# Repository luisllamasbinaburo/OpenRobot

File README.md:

# OpenRobot

OpenRobot is an Open Hardware PCB based on Arduino Nano, especially designed for teaching technology

Once assembled, you can use make multiple projects and robots without welding, just adding or removing components in the dupont headers.

OpenRobot is compatible with a huge number of modules thanks to the multiple outputs. 
Also, is compatible with several DC Converters, and differents IMUs (MPU6050, MPU9050/9250 and L3GD20)

## What can I make with OpenRobot?
Almost any Arduino project you can ever imagine! 

Some of them,
- DC Motors Robot, like obstacle avoider (ultrasonic or Sharp), line follower, self-balancing bot...
- Servo Motor Robot, like 2-DOF Tower, 6-DOF Arms...
- Mosfet output for high current proyects (LED, electromagnets, water pumps)
- Bluetooth projects (HC-05/HC-06), like Android or PC communication, beacons...
- WiFi projects (ESP01), like controlling from Web, MQTT datalogger...
- Temperature, pressure, humidity weather station with BME280
- Any other project, thanks to the multiple available outputs!

## Connectors
A lot of connectos availble, so you can customicce OpenRobot to you project requirement

- 2x DC Motor
- 2x Encoder
- Aux Output 3V3, 5V, Vreg
- 2x I2C 5V + 1x I2C 3V3
- 3x Ultrasonic Sensor
- 3x Analog Input (with optional smd resistor)
- 6x Servo
- 5x IR Sensor
- 3x Mosfet
 
 But, I you wany, can also use any of this output as a GPIO.

## Pinout
Of course, not all the components and outputs are available at the same time, due to Arduino Nano pins numbers.

You have to choose which of this components your project requires. But posibilities are almost ilimited!

This is the pinout of OpenRobot

## Components
OpenRobot allows you to mount several modules to your projects,
- Motor Driver TB6612FNG
- IMU (compatible with several IMUs)
- Temperature/Pressure/Humidity (BMP280/BME280)
- Level shifter (required to use Bluetooth or ESP01)
- Blueooth ESP01
- Bluetooth HC-04/05/06

But you can add a lot of modules thanks to the 3V3 and 5V I2C and UART.

## Powering
Powering is one of the most important point in any project. OpenRobot allow a simple but flexible power management in the proyect
- Power Switch 
- Up to 3 DC Converters (5V, 3V3, +1 Vreg)
- Power selector to select wich components (DC Motors, servo, Mosfet) are powering with each DC converter
- Posible to by-pass DC Converters and powering through Nano regulators (just in low-power and simple projects)
- Battery sense (optional)

### DC Converters
OpenRobot is compatible with two different DC Converters modules.

Just assembly in the right position for you DC Converter model.

### Power selection
Powering selection to device are make using dupong jumper connections.
Outputs to:
- Servo
- DC Motors
- Mosfet

Can be connected to:
- Vregulated
- 5V
- Vbatery

Aditionally, you can completely by-pass DC converters, and use Arduino regulators for 3V3 and/or 5V PCB rails, thus removing the need of installing DC Converters at all.

Only recommended in case of small / low power projects

## IMU
IMU is an important part of most Arduino projects. OpenRobot is compatible with a big number of IMUs, including the most populars. 

Just put your IMU in the right position. In some IMU modules you make need to use the Vcc optional pin to adapt powering to your IMU pinout.

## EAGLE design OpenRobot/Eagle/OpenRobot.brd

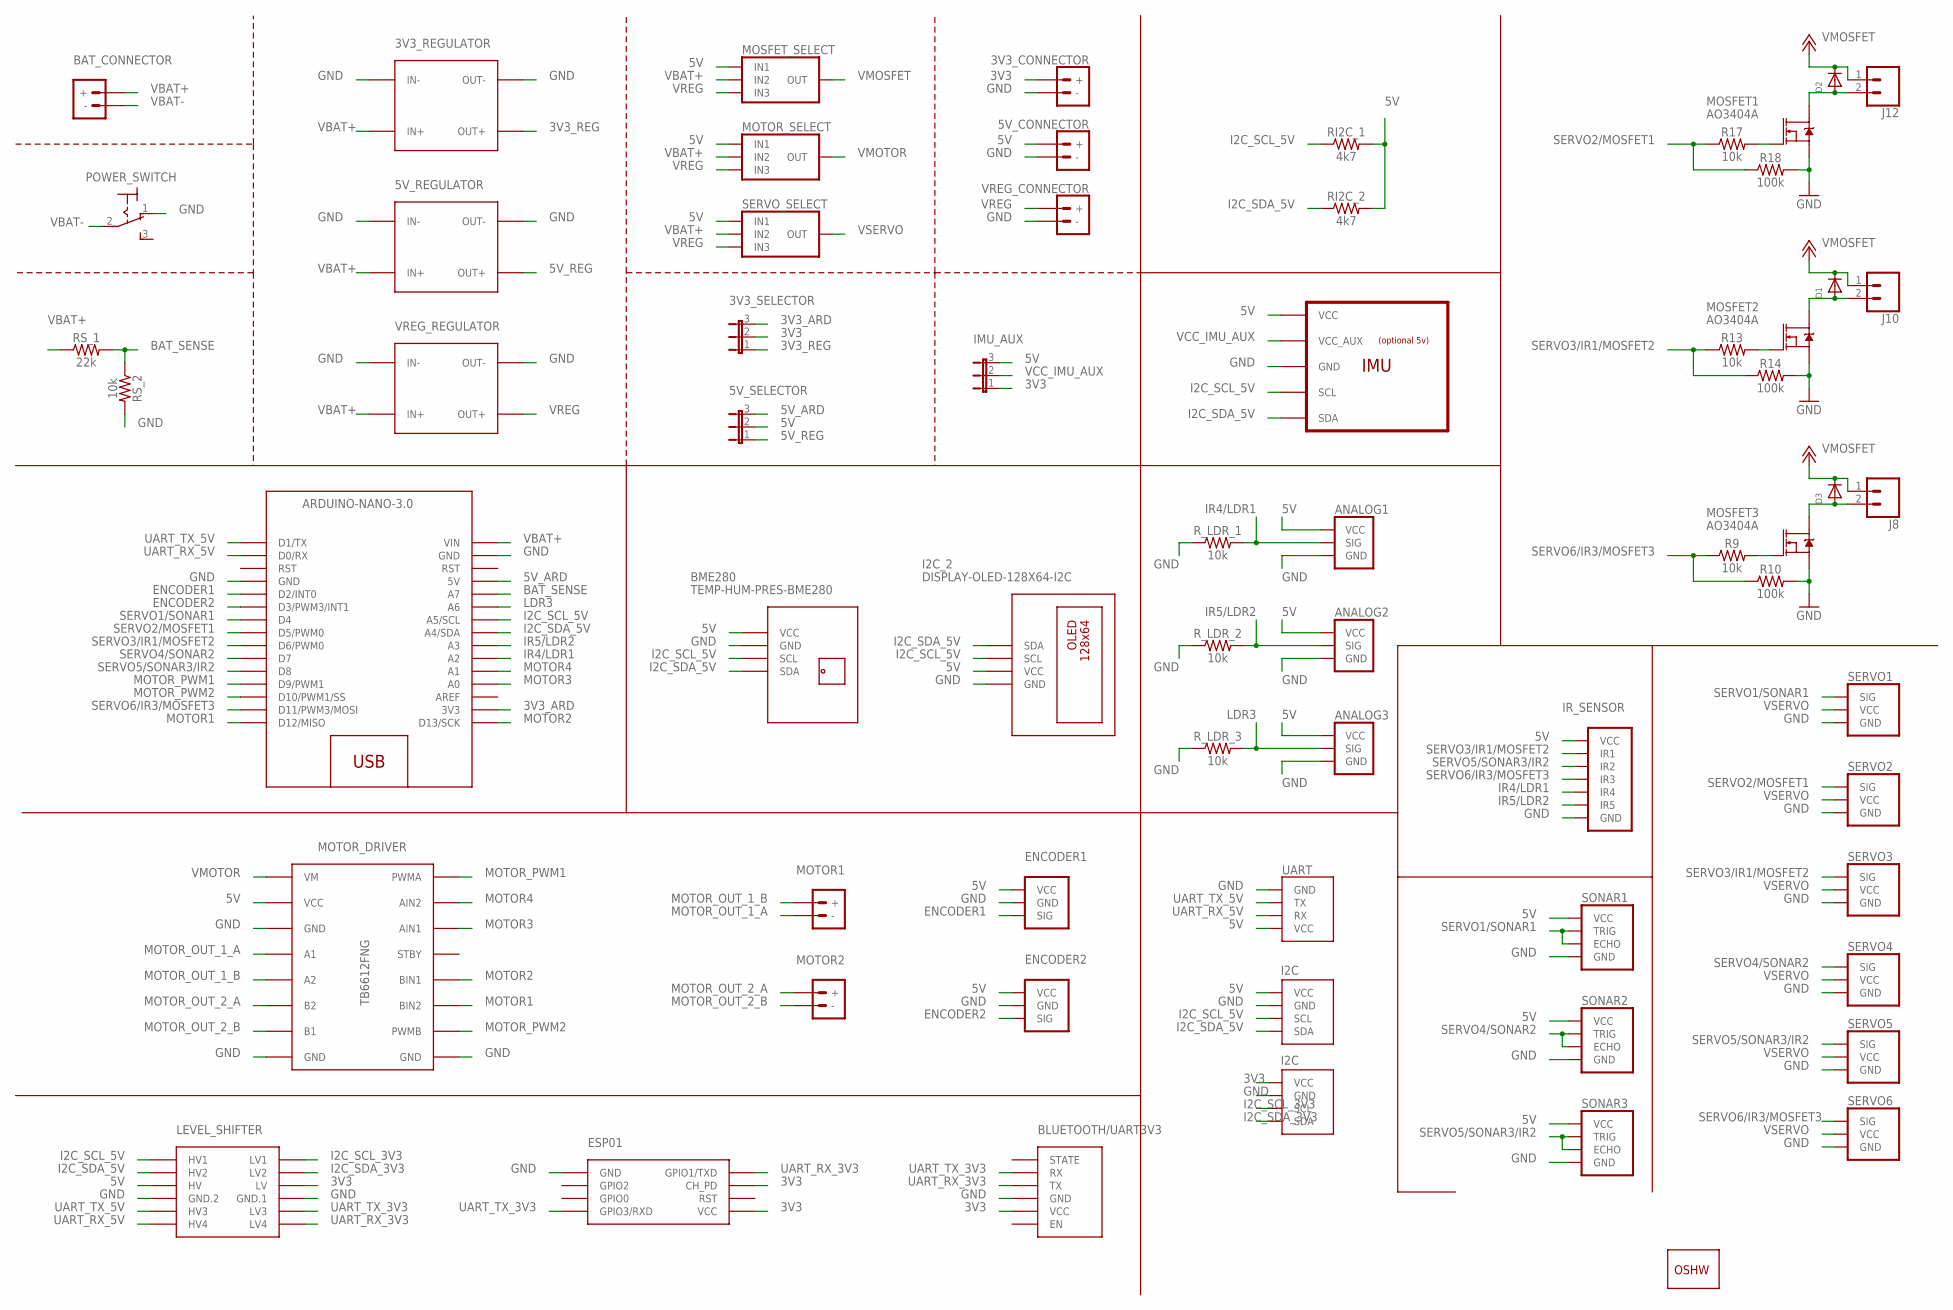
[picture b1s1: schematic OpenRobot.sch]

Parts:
3V3_CONNECTOR, 5V_CONNECTOR: MOTOR-TERMINAL2.54MM_SCREWTERM; 1X02_2.54_SCREWTERM
3V3_REGULATOR, 5V_REGULATOR: MINI-DC-STEP-DOWN-MP2307
3V3_SELECTOR, 5V_SELECTOR: 1; JP2
ANALOG1, ANALOG2, ANALOG3: LDR/OCT; LDR
ARDUINO_NANO1: ARDUINO-NANO-3.0
BAT_CONNECTOR: POWER-TERMINAL5MM; SCREWTERMINAL-5MM-2
BLUETOOTH/UART3V3: BLUETOOTH-HC-05
BME280: TEMP-HUM-PRES-BME280
D1, D2, D3: DIODESOD-123; SOD-123
ENCODER1, ENCODER2: ENCODER/OCT; ENCODER
GOLD_ORB_SM1: OSHWLOGO_GOLD_ORB_MED; OSHW1
I2C_1, I2C_3: I2C; I2C_VCC_GND_SCL_SDA
I2C_2: DISPLAY-OLED-128X64-I2C
IMU_AUX: 1; JP2
IR_SENSOR: IR-5/OCT; IR-5
J8, J10, J12: CONN_02LOCK_LONGPADS; 1X02_LOCK_LONGPADS
LEVEL_SHIFTER: LEVEL-SHIFTER-4CH
MOSFET1, MOSFET2, MOSFET3: AO3404A; SOT23-3
MOSFET_SELECT: JUMPER_3-1
MOTOR1, MOTOR2: MOTOR-TERMINAL5MM; SCREWTERMINAL-5MM-2
MOTOR_DRIVER: TB6612FNG
MOTOR_SELECT: JUMPER_3-1
POWER_SWITCH: LEVER-POWER-SWITCH; M9040P
R9, R13, R17: 10k; 1206
R10, R14, R18: 100k; 1206
RI2C_1, RI2C_2: 4k7; 1206
RS_1: 22k; 1206
RS_2: 10k; 1206
R_LDR_1, R_LDR_2, R_LDR_3: 10k; 1206
SERVO1, SERVO2, SERVO3, SERVO4, SERVO5, SERVO6: SERVOSERVO; SERVO
SERVO_SELECT: JUMPER_3-1
SONAR1, SONAR2, SONAR3: ULTRASONIC/OCT; ULTRASONIC
U1: IMU_6/9/10DOFMPU6050; IMU_6/9/10DOF
U$1: ESP01
UART: UART; GENERIC_UART
VREG_CONNECTOR: MOTOR-TERMINAL2.54MM_SCREWTERM; 1X02_2.54_SCREWTERM
VREG_REGULATOR: MINI-DC-STEP-DOWN-MP2307

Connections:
3V3: 3V3_CONNECTOR.+, 3V3_SELECTOR.2, BLUETOOTH/UART3V3.VCC, I2C_3.VCC, IMU_AUX.1, LEVEL_SHIFTER.J1.3 (LV), U$1.CH_PD, U$1.VCC
3V3_ARD: 3V3_SELECTOR.3, ARDUINO_NANO1.3V3
3V3_REG: 3V3_REGULATOR.OUT2.+ (OUT+), 3V3_REGULATOR.OUT+, 3V3_SELECTOR.1
5V: 5V_CONNECTOR.+, 5V_SELECTOR.2, ANALOG1.VCC, ANALOG2.VCC, ANALOG3.VCC, BME280.VCC, ENCODER1.VCC, ENCODER2.VCC, I2C_1.VCC, I2C_2.VCC, IMU_AUX.3, IR_SENSOR.VCC, LEVEL_SHIFTER.J2.3 (HV), MOSFET_SELECT.IN1, MOTOR_DRIVER.VCC, MOTOR_SELECT.IN1, RI2C_1.2, RI2C_2.2, SERVO_SELECT.IN1, SONAR1.VCC, SONAR2.VCC, SONAR3.VCC, U1.VCC, UART.VCC
5V_ARD: 5V_SELECTOR.3, ARDUINO_NANO1.5V
5V_REG: 5V_REGULATOR.OUT2.+ (OUT+), 5V_REGULATOR.OUT+, 5V_SELECTOR.1
BAT_SENSE: ARDUINO_NANO1.A7, RS_1.2, RS_2.1
ENCODER1: ARDUINO_NANO1.D2 (D2/INT0), ENCODER1.SIG
ENCODER2: ARDUINO_NANO1.D3 (D3/PWM3/INT1), ENCODER2.SIG
GND: 3V3_CONNECTOR.-, 3V3_REGULATOR.IN-, 3V3_REGULATOR.OUT-, 5V_CONNECTOR.-, 5V_REGULATOR.IN-, 5V_REGULATOR.OUT-, ANALOG1.GND, ANALOG2.GND, ANALOG3.GND, ARDUINO_NANO1.GND@1 (GND), ARDUINO_NANO1.GND@2 (GND), BLUETOOTH/UART3V3.GND, BME280.GND, ENCODER1.GND, ENCODER2.GND, I2C_1.GND, I2C_2.GND, I2C_3.GND, IR_SENSOR.GND, LEVEL_SHIFTER.J1.4 (GND.1), LEVEL_SHIFTER.J2.4 (GND.2), MOSFET1.2 (S), MOSFET2.2 (S), MOSFET3.2 (S), MOTOR_DRIVER.GND1 (GND), MOTOR_DRIVER.GND2 (GND), MOTOR_DRIVER.GND3 (GND), POWER_SWITCH.1 (O), R10.2, R14.2, R18.2, RS_2.2, R_LDR_1.1, R_LDR_2.1, R_LDR_3.1, SERVO1.GND, SERVO2.GND, SERVO3.GND, SERVO4.GND, SERVO5.GND, SERVO6.GND, SONAR1.GND, SONAR2.GND, SONAR3.GND, U1.GND, U$1.GND, UART.GND, VREG_CONNECTOR.-, VREG_REGULATOR.IN-, VREG_REGULATOR.OUT-
I2C_SCL_3V3: I2C_3.SCL, LEVEL_SHIFTER.J1.1 (LV1)
I2C_SCL_5V: ARDUINO_NANO1.A5 (A5/SCL), BME280.SCL, I2C_1.SCL, I2C_2.SCL, LEVEL_SHIFTER.J2.1 (HV1), RI2C_1.1, U1.SCL
I2C_SDA_3V3: I2C_3.SDA, LEVEL_SHIFTER.J1.2 (LV2)
I2C_SDA_5V: ARDUINO_NANO1.A4 (A4/SDA), BME280.SDA, I2C_1.SDA, I2C_2.SDA, LEVEL_SHIFTER.J2.2 (HV2), RI2C_2.1, U1.SDA
IR4/LDR1: ANALOG1.SIG, ARDUINO_NANO1.A2, IR_SENSOR.4 (IR4), R_LDR_1.2
IR5/LDR2: ANALOG2.SIG, ARDUINO_NANO1.A3, IR_SENSOR.5 (IR5), R_LDR_2.2
LDR3: ANALOG3.SIG, ARDUINO_NANO1.A6, R_LDR_3.2
MOTOR1: ARDUINO_NANO1.D12 (D12/MISO), MOTOR_DRIVER.BIN2
MOTOR2: ARDUINO_NANO1.D13 (D13/SCK), MOTOR_DRIVER.BIN1
MOTOR3: ARDUINO_NANO1.A0, MOTOR_DRIVER.AIN1
MOTOR4: ARDUINO_NANO1.A1, MOTOR_DRIVER.AIN2
MOTOR_OUT_1_A: MOTOR1.-, MOTOR_DRIVER.A1
MOTOR_OUT_1_B: MOTOR1.+, MOTOR_DRIVER.A2
MOTOR_OUT_2_A: MOTOR2.+, MOTOR_DRIVER.B2
MOTOR_OUT_2_B: MOTOR2.-, MOTOR_DRIVER.B1
MOTOR_PWM1: ARDUINO_NANO1.D9 (D9/PWM1), MOTOR_DRIVER.PWMA
MOTOR_PWM2: ARDUINO_NANO1.D10 (D10/PWM1/SS), MOTOR_DRIVER.PWMB
unnamed: MOSFET3.1 (G), R9.2
unnamed: D3.A, J8.2, MOSFET3.3 (D)
unnamed: MOSFET2.1 (G), R13.2
unnamed: D1.A, J10.2, MOSFET2.3 (D)
unnamed: MOSFET1.1 (G), R17.2
unnamed: D2.A, J12.2, MOSFET1.3 (D)
SERVO1/SONAR1: ARDUINO_NANO1.D4, SERVO1.SIG, SONAR1.ECHO, SONAR1.TRIG
SERVO2/MOSFET1: ARDUINO_NANO1.D5 (D5/PWM0), R17.1, R18.1, SERVO2.SIG
SERVO3/IR1/MOSFET2: ARDUINO_NANO1.D6 (D6/PWM0), IR_SENSOR.1 (IR1), R13.1, R14.1, SERVO3.SIG
SERVO4/SONAR2: ARDUINO_NANO1.D7, SERVO4.SIG, SONAR2.ECHO, SONAR2.TRIG
SERVO5/SONAR3/IR2: ARDUINO_NANO1.D8, IR_SENSOR.2 (IR2), SERVO5.SIG, SONAR3.ECHO, SONAR3.TRIG
SERVO6/IR3/MOSFET3: ARDUINO_NANO1.D11 (D11/PWM3/MOSI), IR_SENSOR.3 (IR3), R9.1, R10.1, SERVO6.SIG
UART_RX_3V3: BLUETOOTH/UART3V3.TX, LEVEL_SHIFTER.J1.6 (LV4), U$1.TX (GPIO1/TXD)
UART_RX_5V: ARDUINO_NANO1.RX0 (D0/RX), LEVEL_SHIFTER.J2.6 (HV4), UART.RX
UART_TX_3V3: BLUETOOTH/UART3V3.RX, LEVEL_SHIFTER.J1.5 (LV3), U$1.RX (GPIO3/RXD)
UART_TX_5V: ARDUINO_NANO1.TX1 (D1/TX), LEVEL_SHIFTER.J2.5 (HV3), UART.TX
VBAT+: 3V3_REGULATOR.IN+, 3V3_REGULATOR.IN.2+ (IN+), 5V_REGULATOR.IN+, 5V_REGULATOR.IN.2+ (IN+), ARDUINO_NANO1.VIN, BAT_CONNECTOR.+, MOSFET_SELECT.IN2, MOTOR_SELECT.IN2, RS_1.1, SERVO_SELECT.IN2, VREG_REGULATOR.IN+, VREG_REGULATOR.IN.2+ (IN+)
VBAT-: BAT_CONNECTOR.-, POWER_SWITCH.2
VCC_IMU_AUX: IMU_AUX.2, U1.VCC_AUX
VMOSFET: D1.C, D2.C, D3.C, J8.1, J10.1, J12.1, MOSFET_SELECT.OUT
VMOTOR: MOTOR_DRIVER.VM, MOTOR_SELECT.OUT
VREG: MOSFET_SELECT.IN3, MOTOR_SELECT.IN3, SERVO_SELECT.IN3, VREG_CONNECTOR.+, VREG_REGULATOR.OUT2.+ (OUT+), VREG_REGULATOR.OUT+
VSERVO: SERVO1.VCC, SERVO2.VCC, SERVO3.VCC, SERVO4.VCC, SERVO5.VCC, SERVO6.VCC, SERVO_SELECT.OUT

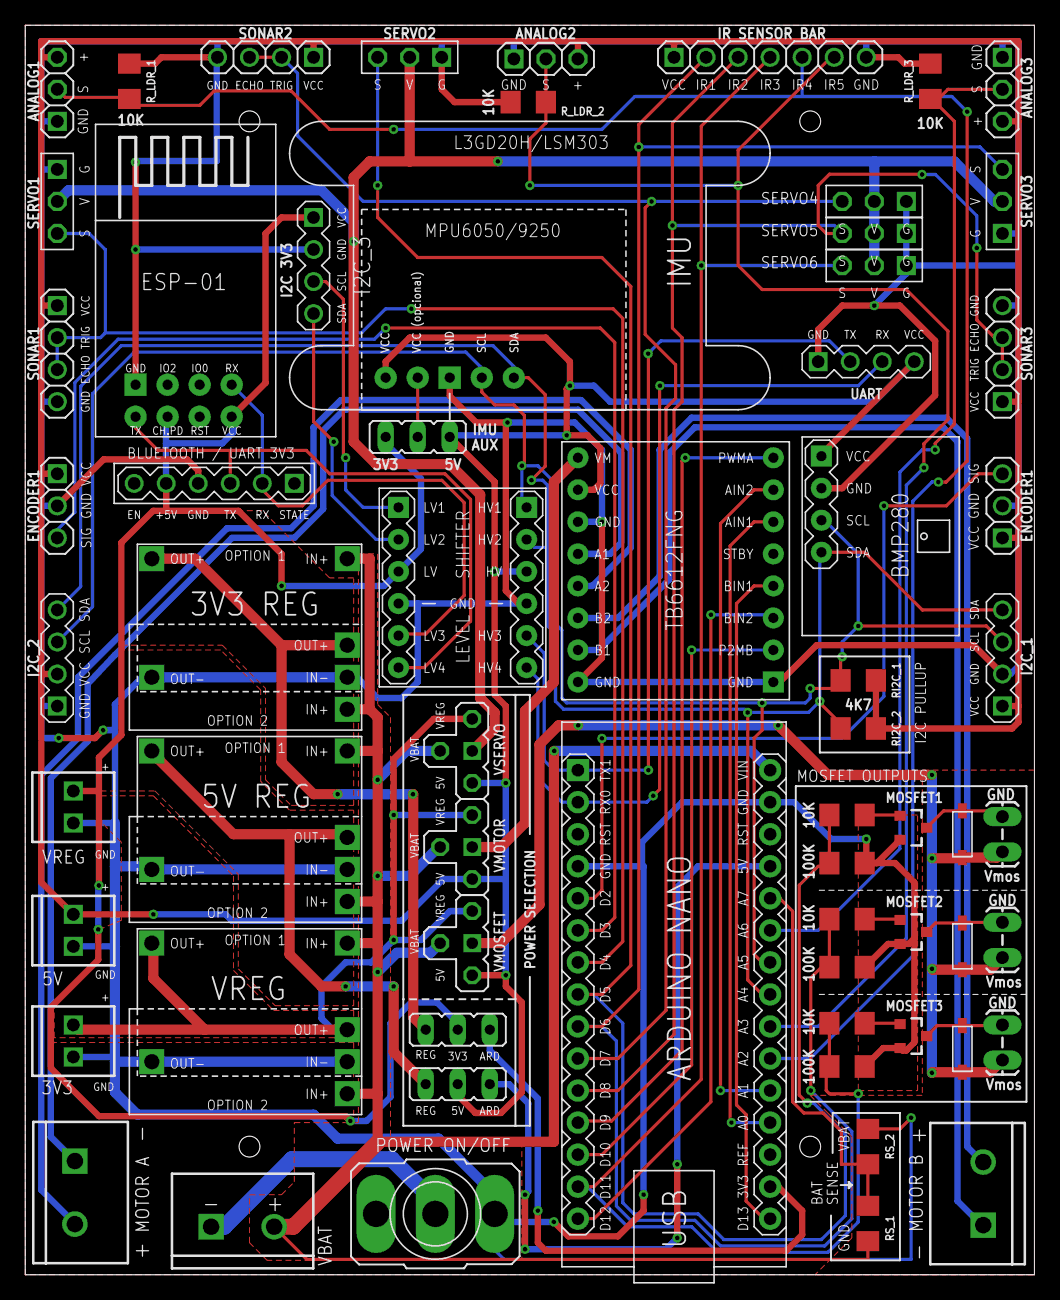
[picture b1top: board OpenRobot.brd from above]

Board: 2 copper layers, 80.0 x 99.1 mm, 65 parts (1 on the bottom side), 50 nets.

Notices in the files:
parts and their libraries:
SparkFun-DiscreteSemi: Licensing: Creative Commons ShareAlike 4.0 International - https://creativecommons.org/licenses/by-sa/4.0
